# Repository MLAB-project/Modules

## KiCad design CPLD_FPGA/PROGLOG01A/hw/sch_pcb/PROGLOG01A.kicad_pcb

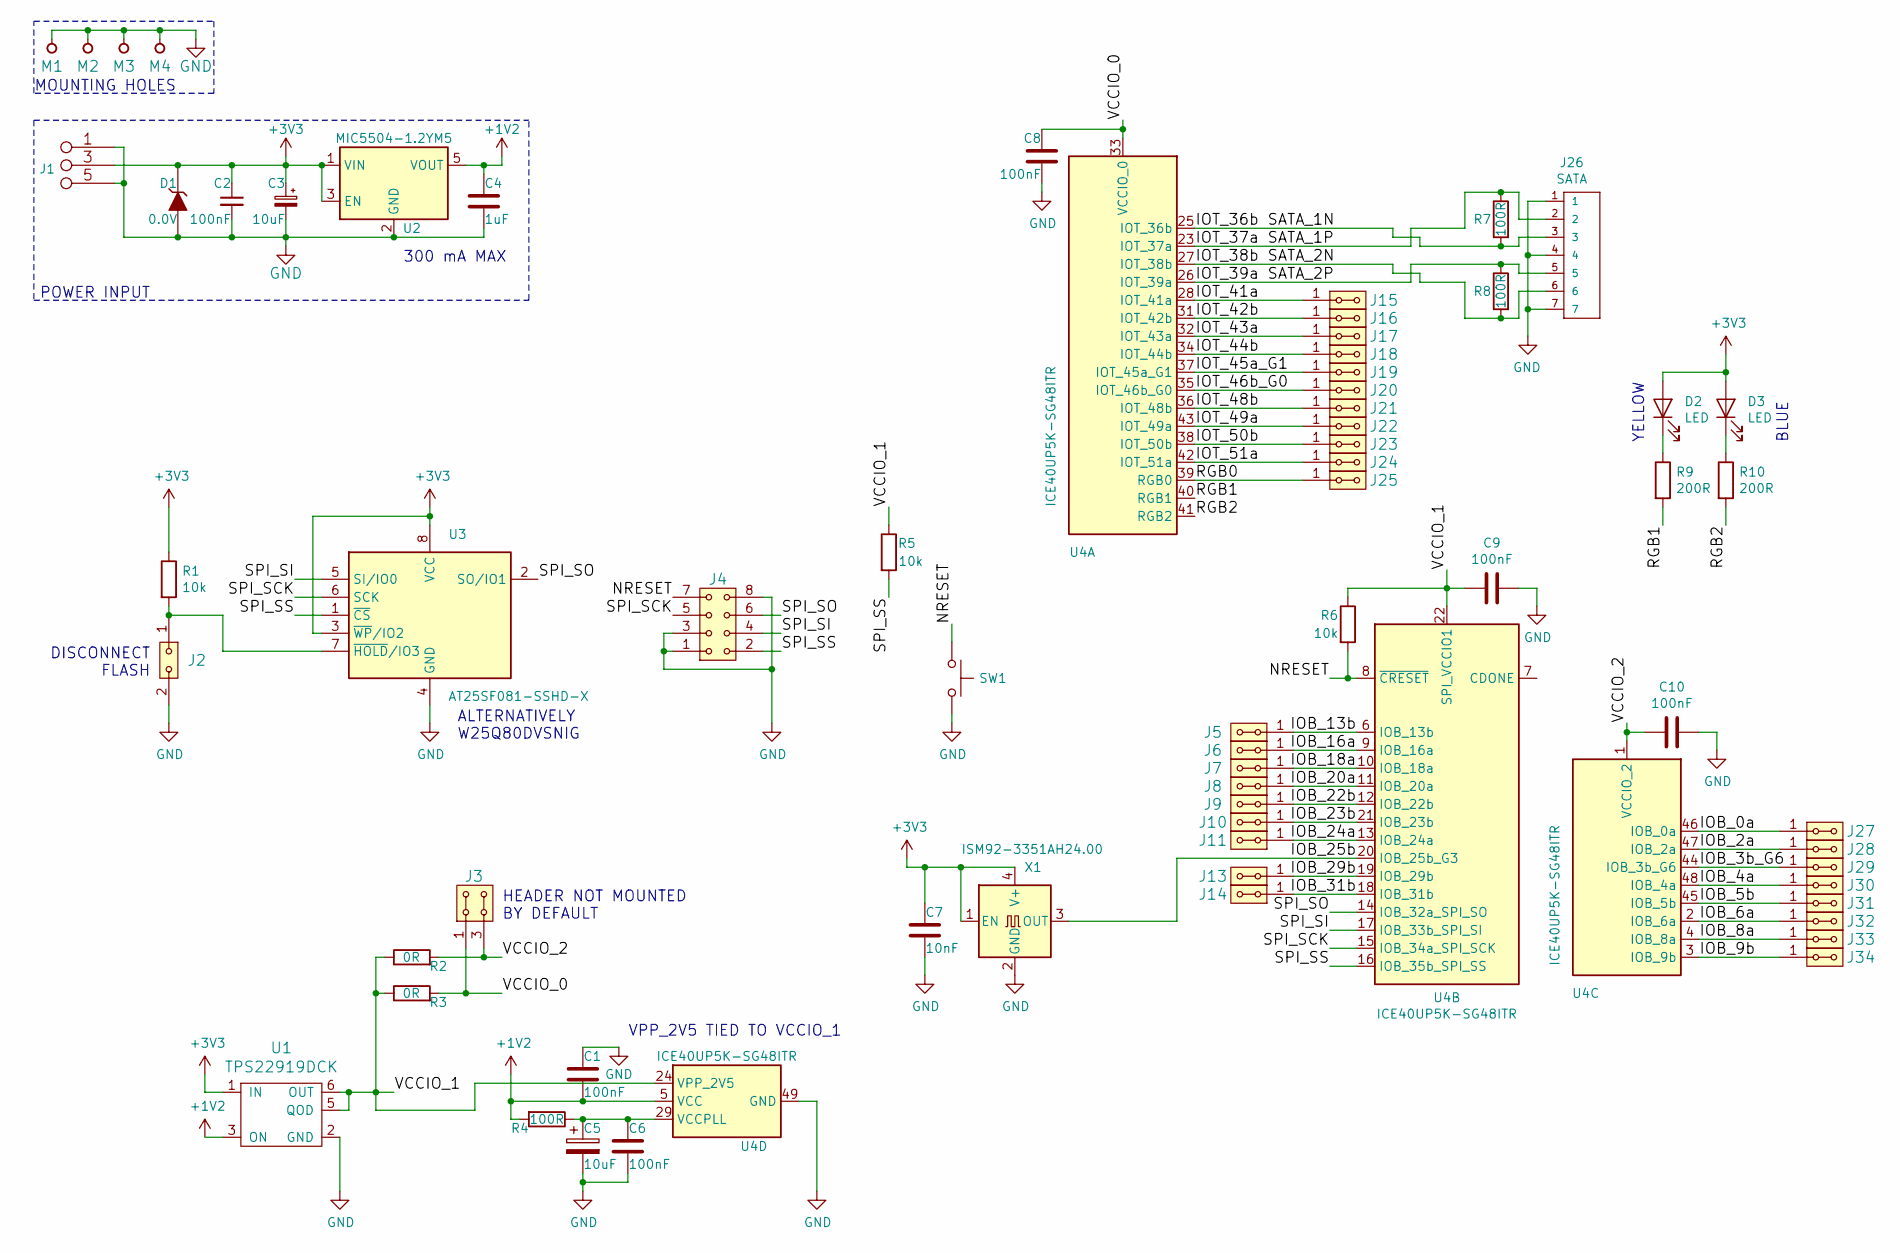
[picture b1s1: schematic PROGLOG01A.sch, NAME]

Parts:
C1, C2, C6, C8, C9, C10: 100nF; SMD-0805
C3, C5: 10uF; SMD-0805
C4: 1uF; SMD-0805
C7: 10nF; SMD-0805
D1: 0.0V; Diode-MiniMELF_Standard
D2, D3: LED; LED_1206
J1: JUMP_3X2; Straight_2x03
J2: HEADER_2x01; Straight_2x01
J3: HEADER_2x02_PARALLEL; Straight_2x02
J4: HEADER_2x04; Straight_2x04
J5, J6, J7, J8, J9, J10, J11, J13, J14, J15, J16, J17, J18, J19, J20, J21, J22, J23, J24, J25, J27, J28, J29, J30, J31, J32, J33, J34: HEADER_2x01_PARALLEL; Straight_2x01
J26: SATA; SATA-7_THT_VERT_2
M1, M2, M3, M4: HOLE; MountingHole_3mm
R1, R5, R6: 10k; SMD-0805
R2, R3: 0R; SMD-0805
R4, R7, R8: 100R; SMD-0805
R9, R10: 200R; SMD-0805
SW1: SW_Push; SW_PUSH_SMALL
U1: TPS22919DCK; SOT-363_SC-70-6_Handsoldering
U2: MIC5504-1.2YM5; SOT-23-5_HandSoldering
U3: AT25SF081-SSHD-X; SOIC-8_3.9x4.9mm_Pitch1.27mm
U4: ICE40UP5K-SG48ITR; QFN-48-1EP_7x7mm_P0.5mm_EP5.6x5.6mm
X1: ISM92-3351AH24.00; ISM92

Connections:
+1V2: C1.2, C4.1, R4.2, U1.3 (ON), U2.5 (VOUT), U4.5 (VCC), U4.30 (VCC)
+3V3: C2.1, C3.1, C7.1, D1.1 (K), D2.2 (A), D3.2 (A), J1.3 (4), J1.4, R1.1, U1.1 (IN), U2.1 (VIN), U2.3 (EN), U3.3 (~WP~/IO2), U3.8 (VCC), X1.1 (EN), X1.4 (V+)
/IOB_0a: J27.1, J27.2, U4.46 (IOB_0a)
/IOB_2a: J28.1, J28.2, U4.47 (IOB_2a)
/IOB_3b_G6: J29.1, J29.2, U4.44 (IOB_3b_G6)
/IOB_4a: J30.1, J30.2, U4.48 (IOB_4a)
/IOB_5b: J31.1, J31.2, U4.45 (IOB_5b)
/IOB_6a: J32.1, J32.2, U4.2 (IOB_6a)
/IOB_8a: J33.1, J33.2, U4.4 (IOB_8a)
/IOB_9b: J34.1, J34.2, U4.3 (IOB_9b)
/IOB_13b: J5.1, J5.2, U4.6 (IOB_13b)
/IOB_16a: J6.1, J6.2, U4.9 (IOB_16a)
/IOB_18a: J7.1, J7.2, U4.10 (IOB_18a)
/IOB_20a: J8.1, J8.2, U4.11 (IOB_20a)
/IOB_22b: J9.1, J9.2, U4.12 (IOB_22b)
/IOB_23b: J10.1, J10.2, U4.21 (IOB_23b)
/IOB_24a: J11.1, J11.2, U4.13 (IOB_24a)
/IOB_25b: U4.20 (IOB_25b_G3), X1.3 (OUT)
/IOB_29b: J13.1, J13.2, U4.19 (IOB_29b)
/IOB_31b: J14.1, J14.2, U4.18 (IOB_31b)
/IOT_41a: J15.1, J15.2, U4.28 (IOT_41a)
/IOT_42b: J16.1, J16.2, U4.31 (IOT_42b)
/IOT_43a: J17.1, J17.2, U4.32 (IOT_43a)
/IOT_44b: J18.1, J18.2, U4.34 (IOT_44b)
/IOT_45a_G1: J19.1, J19.2, U4.37 (IOT_45a_G1)
/IOT_46b_G0: J20.1, J20.2, U4.35 (IOT_46b_G0)
/IOT_48b: J21.1, J21.2, U4.36 (IOT_48b)
/IOT_49a: J22.1, J22.2, U4.43 (IOT_49a)
/IOT_50b: J23.1, J23.2, U4.38 (IOT_50b)
/IOT_51a: J24.1, J24.2, U4.42 (IOT_51a)
/NRESET: J4.7, R6.2, SW1.1, U4.8 (~CRESET)
/RGB0: J25.1, J25.2, U4.39 (RGB0)
/RGB1: R9.2, U4.40 (RGB1)
/RGB2: R10.2, U4.41 (RGB2)
/SATA_1N: J26.3, R7.2, U4.25 (IOT_36b)
/SATA_1P: J26.2, R7.1, U4.23 (IOT_37a)
/SATA_2N: J26.6, R8.2, U4.27 (IOT_38b)
/SATA_2P: J26.5, R8.1, U4.26 (IOT_39a)
/SPI_SCK: J4.5, U3.6 (SCK), U4.15 (IOB_34a_SPI_SCK)
/SPI_SI: J4.4, U3.5 (SI/IO0), U4.17 (IOB_33b_SPI_SI)
/SPI_SO: J4.6, U3.2 (SO/IO1), U4.14 (IOB_32a_SPI_SO)
/SPI_SS: J4.2, R5.2, U3.1 (~CS), U4.16 (IOB_35b_SPI_SS)
/VCCIO_0: C8.1, J3.1, J3.2, R3.2, U4.33 (VCCIO_0)
/VCCIO_1: C9.2, R2.1, R3.1, R5.1, R6.1, U1.5 (QOD), U1.6 (OUT), U4.22 (SPI_VCCIO1), U4.24 (VPP_2V5)
/VCCIO_2: C10.2, J3.3, J3.4, R2.2, U4.1 (VCCIO_2)
GND: C1.1, C2.2, C3.2, C4.2, C5.2, C6.2, C7.2, C8.2, C9.1, C10.1, D1.2 (A), J1.1 (2), J1.2, J1.5 (6), J1.6, J2.2, J4.1, J4.3, J4.8, J26.1, J26.4, J26.7, M1.1, M2.1, M3.1, M4.1, SW1.2, U1.2 (GND), U2.2 (GND), U3.4 (GND), U4.49 (GND), X1.2 (GND)
unnamed: C5.1, C6.1, R4.1, U4.29 (VCCPLL)
unnamed: D2.1 (K), R9.1
unnamed: D3.1 (K), R10.1
unnamed: J2.1, R1.2, U3.7 (~HOLD~/IO3)

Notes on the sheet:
POWER INPUT
MOUNTING HOLES
300 mA MAX
VPP_2V5 TIED TO VCCIO_1
HEADER NOT MOUNTED BY DEFAULT
ALTERNATIVELY W25Q80DVSNIG
DISCONNECT FLASH
YELLOW
BLUE

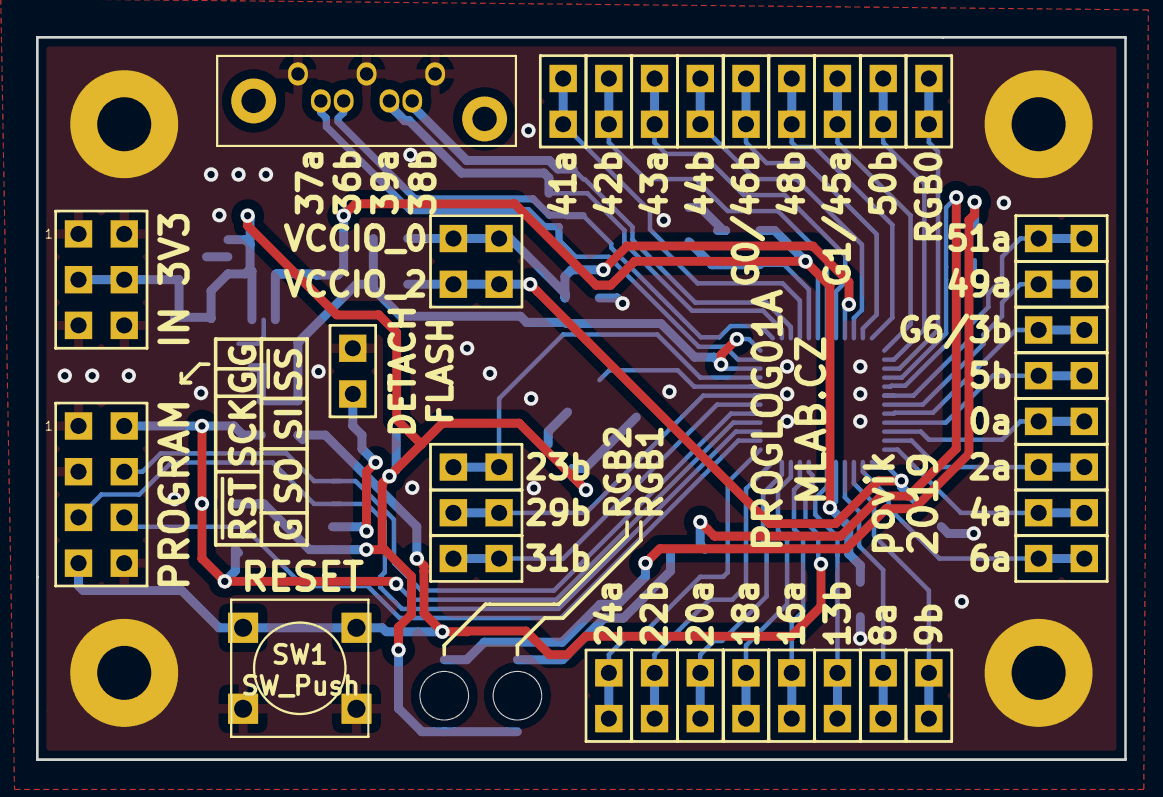
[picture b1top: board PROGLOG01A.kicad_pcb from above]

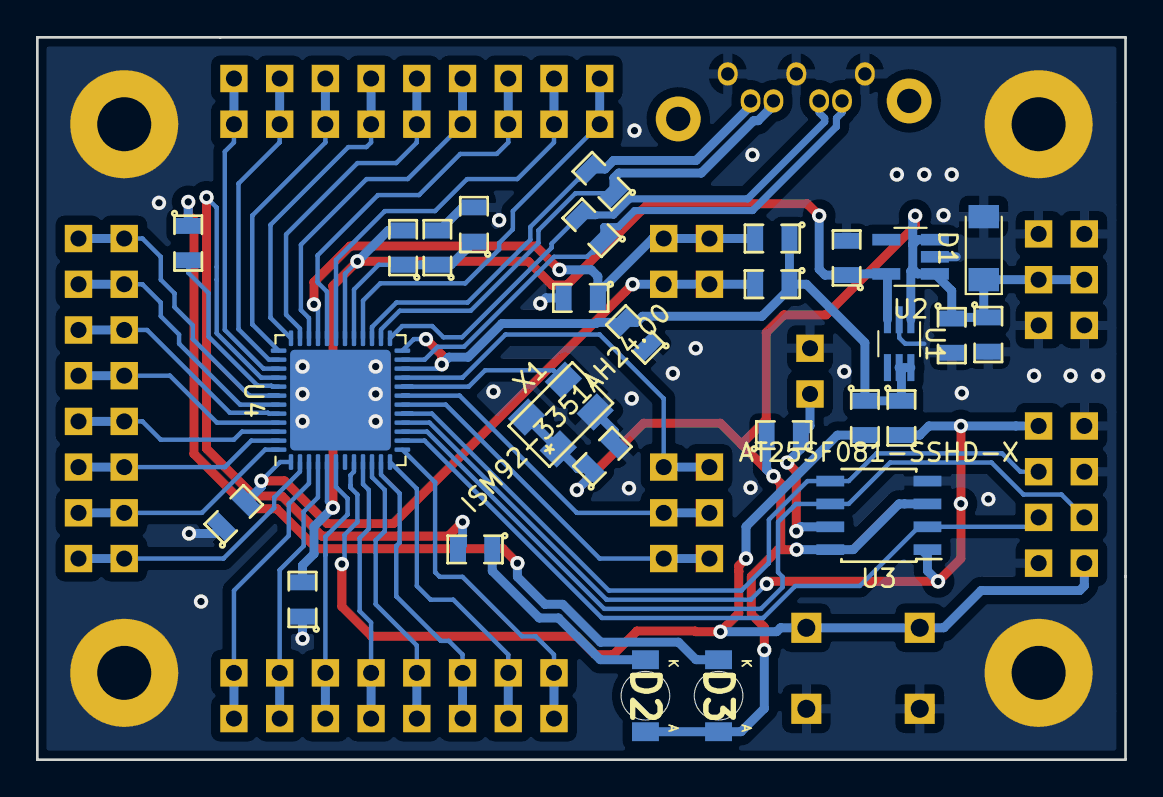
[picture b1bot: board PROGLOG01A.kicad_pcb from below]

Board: 2 copper layers, 60.5 x 40.1 mm, 66 parts (28 on the bottom side), 50 nets.

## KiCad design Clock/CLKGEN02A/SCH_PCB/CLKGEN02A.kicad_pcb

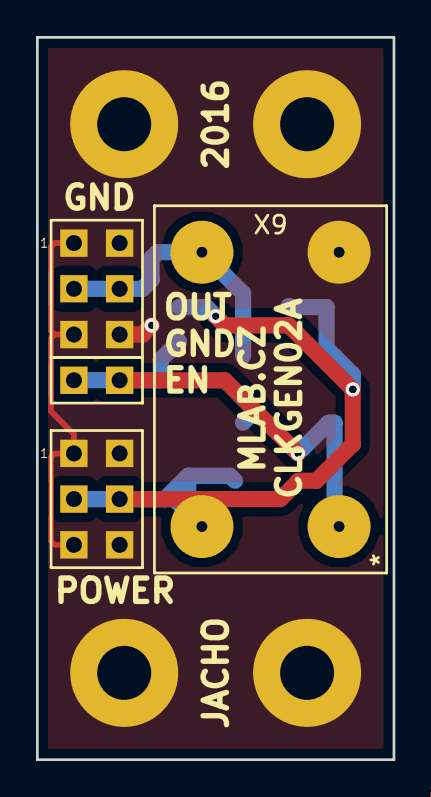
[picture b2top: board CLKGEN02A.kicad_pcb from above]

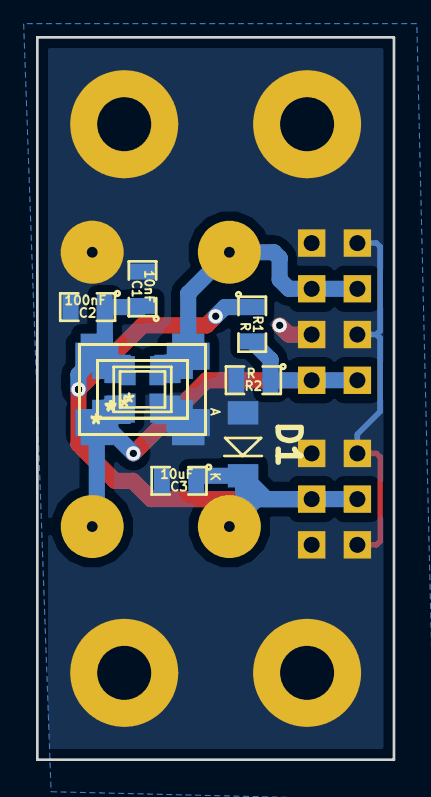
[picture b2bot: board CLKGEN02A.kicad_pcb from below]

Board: 2 copper layers, 19.8 x 40.1 mm, 21 parts (13 on the bottom side), 4 nets.

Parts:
C1: 10nF; SMD-0805
C2: 100nF; SMD-0805
C3: 10uF; SMD-0805
D1: BZV55C; Diode-MiniMELF_Standard
J1, J3: JUMP_3X2; Straight_2x03
J2: JUMP_2x1; Straight_1x02
M1, M2, M3, M4: HOLE; MountingHole_3mm
R1, R2: R; SMD-0805
X1: ASFL1, ASFLK; ASFL1
X2: CFPS-72,CFPS-73; CFPS-72,73
X3: ISM92
X4: ISM97
X6: I533_I534_I733_I734_Series; I533_1534_1733_1734
X7: ISM81
X8: ISM95
X9: OSC-F

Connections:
/EN: J2.1, J2.2, R1.2, R2.1, X1.1, X2.1, X3.1, X4.1, X6.1, X7.1, X8.1, X9.1
/OUT: J3.3, J3.4, X1.3, X2.3, X3.3, X4.3, X6.3, X7.3, X8.3, X9.3
GND: C1.2, C2.2, C3.2, D1.2, J1.1, J1.2, J1.5, J1.6, J3.1, J3.2, J3.5, J3.6, M1.1, M2.1, M3.1, M4.1, R2.2, X1.2, X2.2, X3.2, X4.2, X6.2, X7.2, X8.2, X9.2
VCC: C1.1, C2.1, C3.1, D1.1, J1.3, J1.4, R1.1, X1.4, X2.4, X3.4, X4.4, X6.4, X7.4, X8.4, X9.4

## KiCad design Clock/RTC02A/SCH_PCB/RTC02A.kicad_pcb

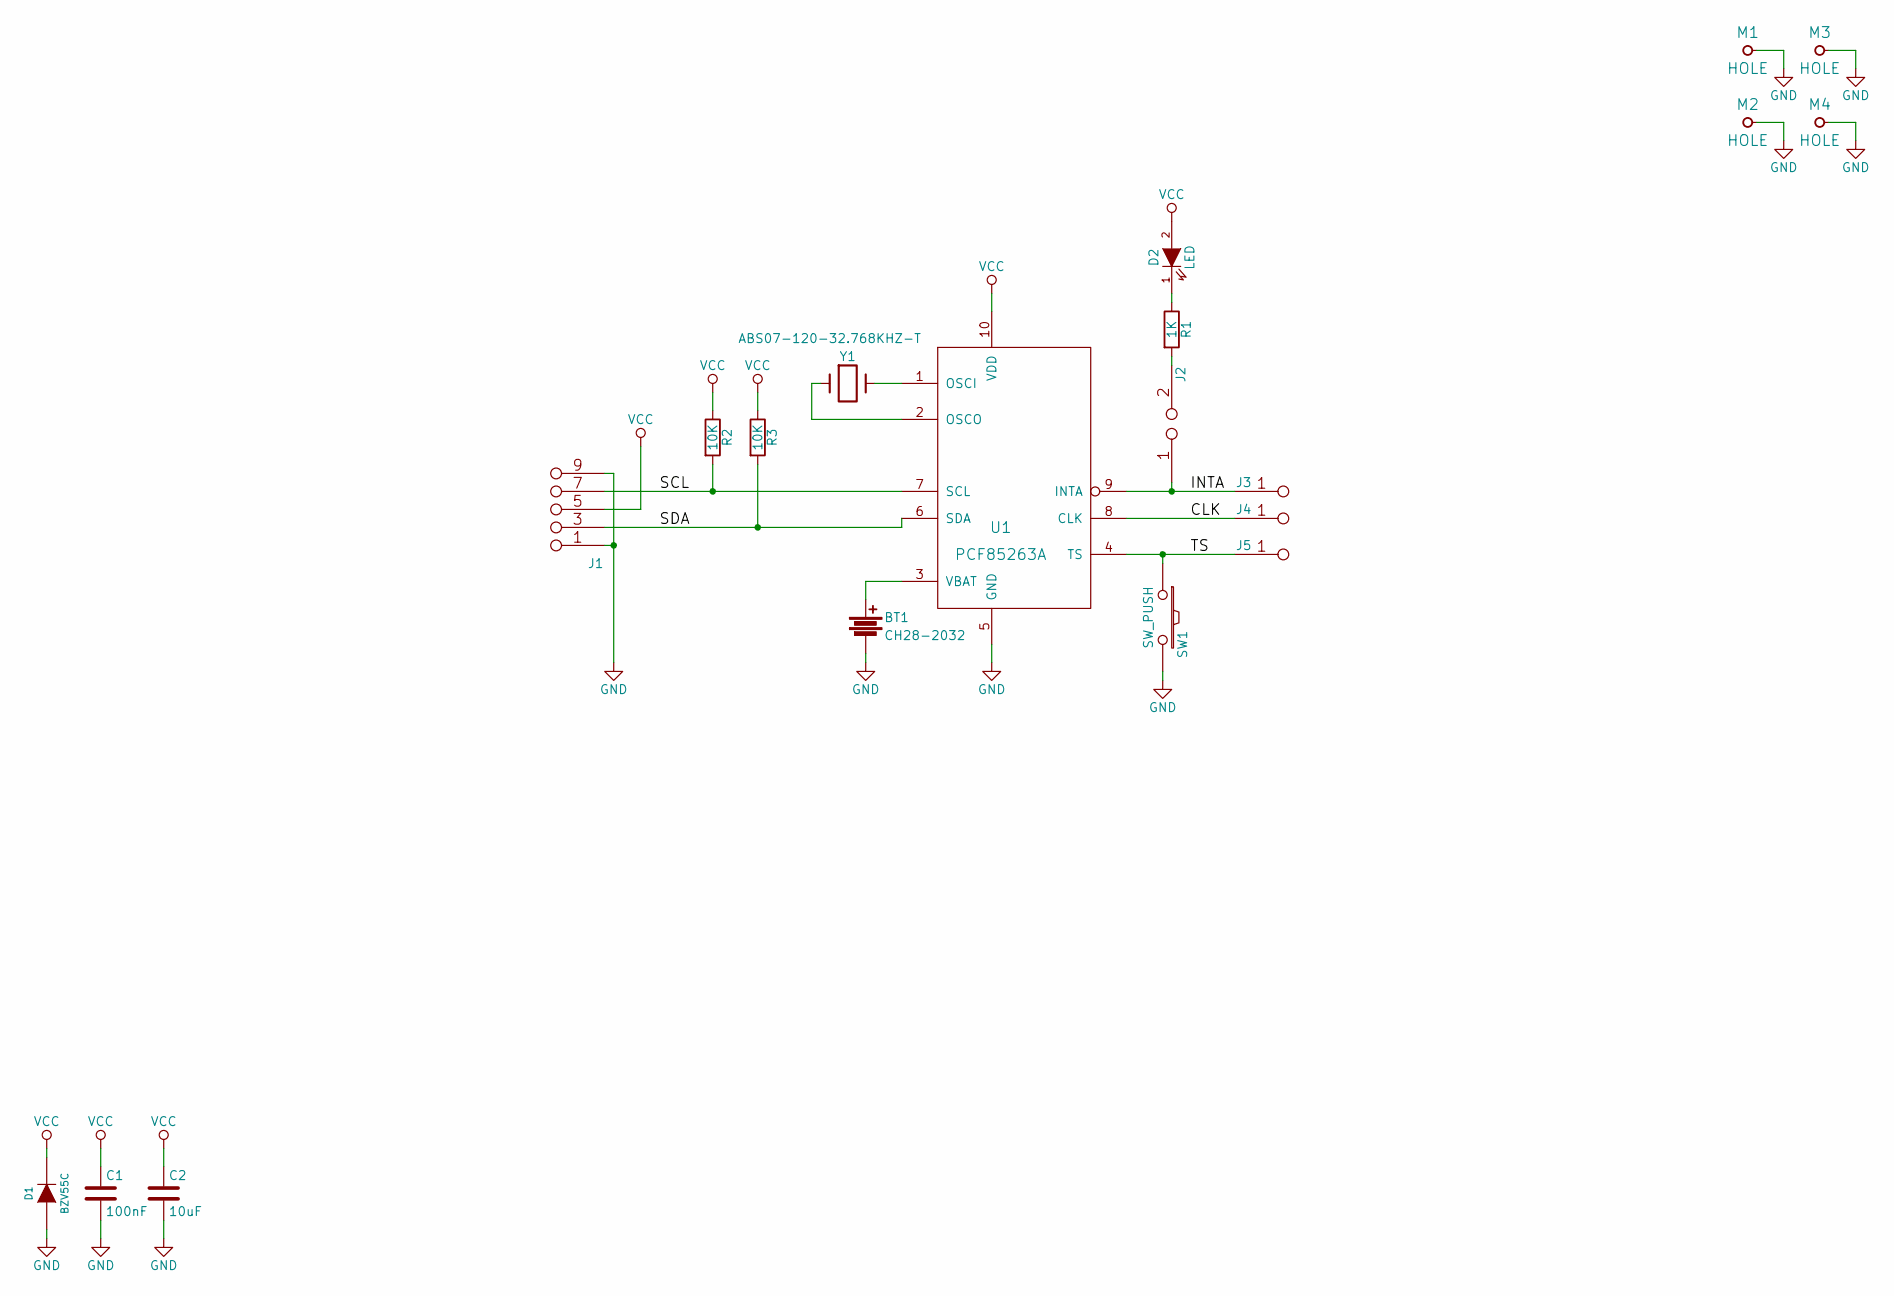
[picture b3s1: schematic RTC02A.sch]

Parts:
BT1: CH28-2032
C1: 100nF; SMD-0805
C2: 10uF; SMD-0805
D1: BZV55C; Diode-MiniMELF_Standard
D2: LED; LED_1206
J1: JUMP_5X2; Straight_2x05
J2: JUMP2_2x1; Straight_2x01
J3, J4, J5: JUMP_2x1; Straight_2x01
M1, M2, M3, M4: HOLE; MountingHole_3mm
R1: 1K; SMD-0805
R2, R3: 10K; SMD-0805
SW1: SW_PUSH; SW_PUSH_SMALL
U1: PCF85263A; TSSOP-10_3x3mm_Pitch0.5mm
Y1: ABS07-120-32.768KHZ-T; ABS07

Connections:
/CLK: J4.1, J4.2, U1.8 (CLK)
/INTA: J2.1, J3.1, J3.2, U1.9 (INTA)
/SCL: J1.7, J1.8 (7), R2.2, U1.7 (SCL)
/SDA: J1.3 (4), J1.4, R3.2, U1.6 (SDA)
/TS: J5.1, J5.2, SW1.1, U1.4 (TS)
GND: BT1.2, C1.2, C2.2, D1.2 (A), J1.1 (2), J1.2, J1.9 (10), J1.10, M1.1, M2.1, M3.1, M4.1, SW1.2, U1.5 (GND); also elsewhere on the board
unnamed: BT1.1, U1.3 (VBAT)
unnamed: D2.1 (K), R1.1
unnamed: J2.2, R1.2
unnamed: U1.1 (OSCI), Y1.2
unnamed: U1.2 (OSCO), Y1.1
VCC: C1.1, C2.1, D1.1 (K), D2.2 (A), J1.5 (6), J1.6, R2.1, R3.1, U1.10 (VDD)

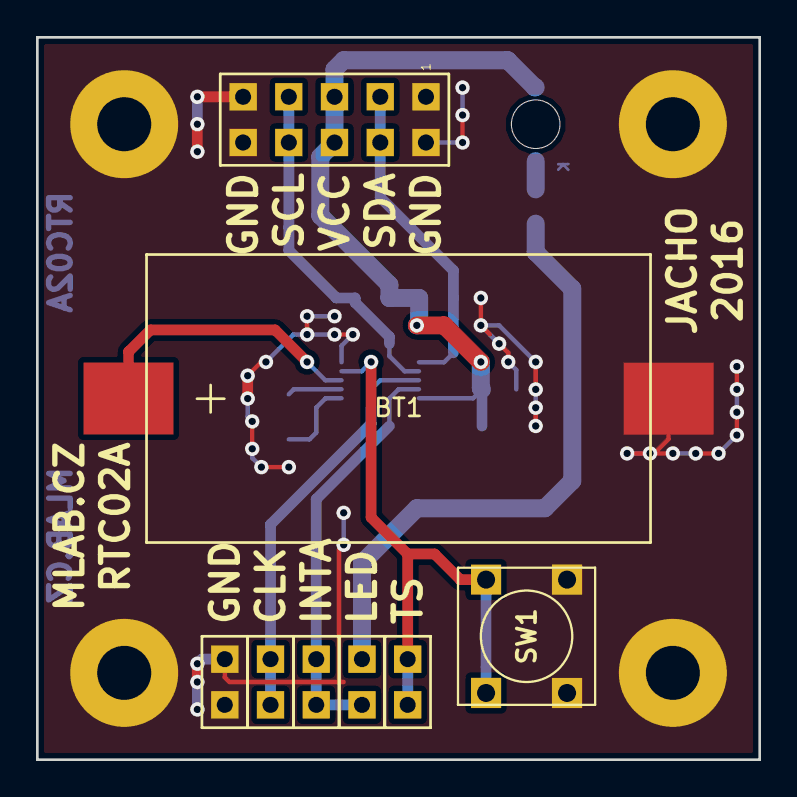
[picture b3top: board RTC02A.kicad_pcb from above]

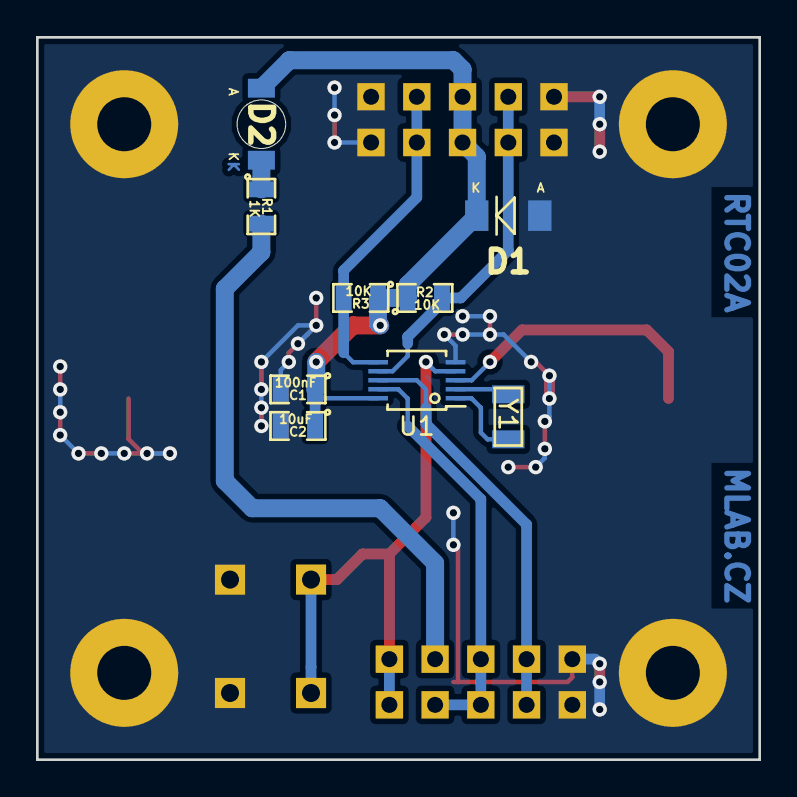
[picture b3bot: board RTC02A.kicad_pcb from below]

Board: 2 copper layers, 40.1 x 40.1 mm, 21 parts (9 on the bottom side), 12 nets.

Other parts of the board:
J6: JUMP_2x1; Straight_2x01

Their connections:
GND: J6.1, J6.2; also elsewhere on the board

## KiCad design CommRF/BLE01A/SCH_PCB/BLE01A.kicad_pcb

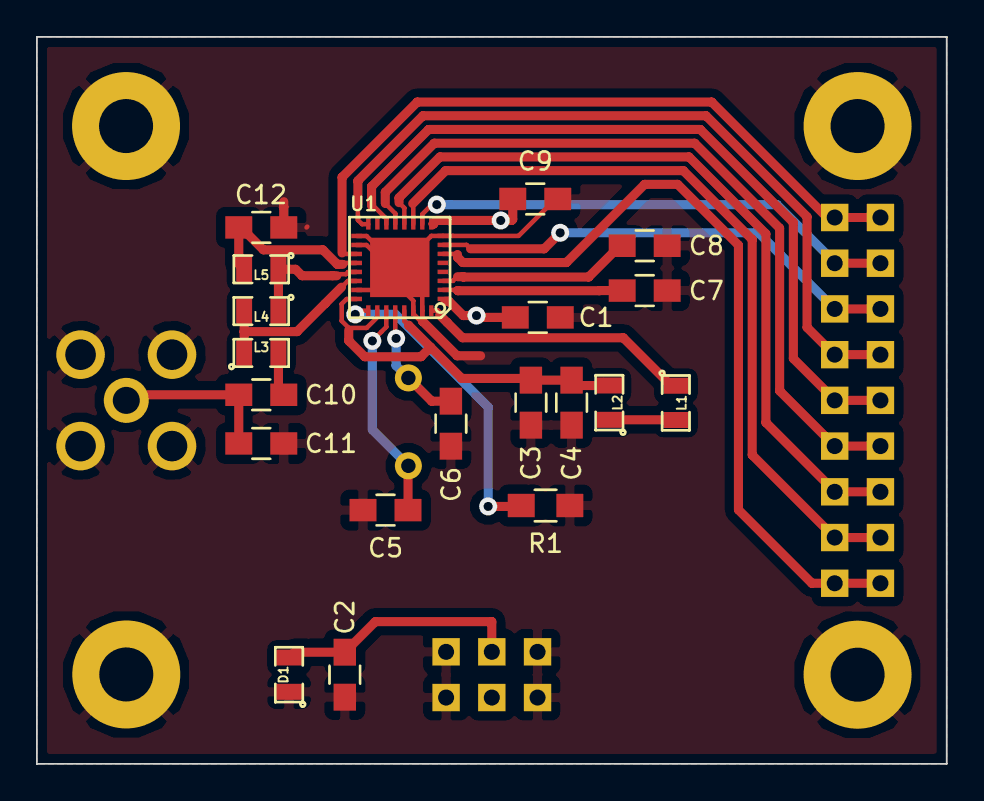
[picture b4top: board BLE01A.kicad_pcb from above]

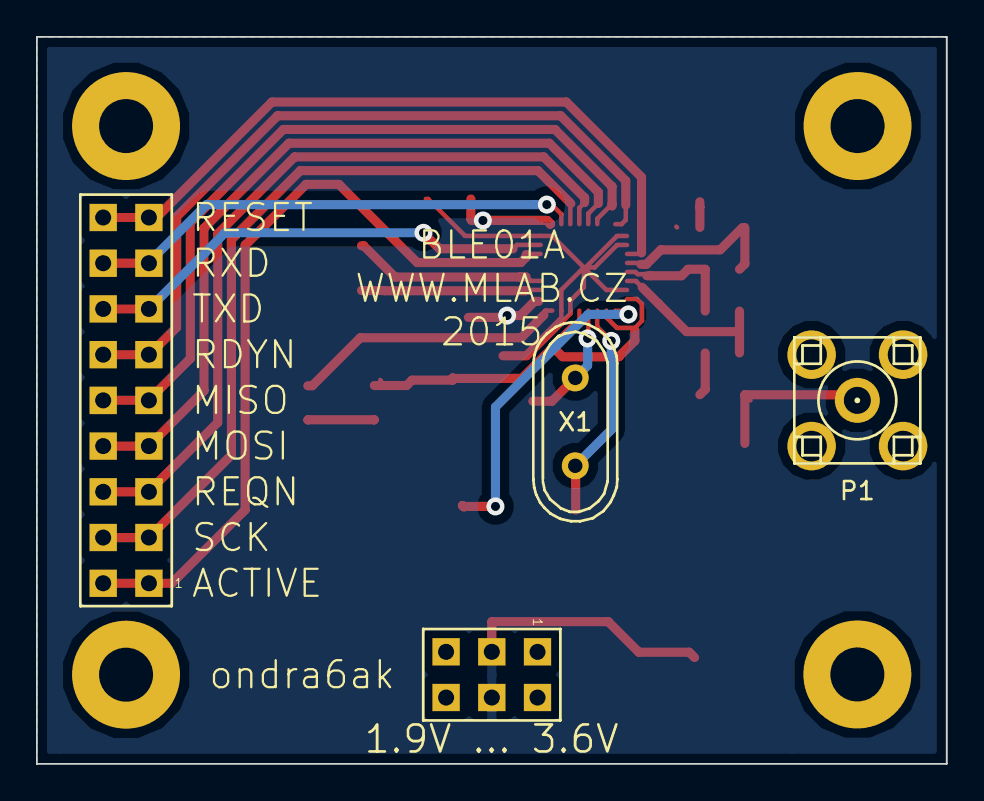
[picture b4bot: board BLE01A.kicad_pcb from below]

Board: 2 copper layers, 50.5 x 40.4 mm, 28 parts (4 on the bottom side), 24 nets.

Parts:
C1, C7, C9: 100nF; C_0805_HandSoldering
C2: 22uF/6.3V; C_0805_HandSoldering
C3: 1nF; C_0805_HandSoldering
C4: 1uF; C_0805_HandSoldering
C5, C6: 12pF; C_0805_HandSoldering
C8: 33nF; C_0805_HandSoldering
C10: 1.8pF; C_0805_HandSoldering
C11: 1.2pF; C_0805_HandSoldering
C12: 2.2nF; C_0805_HandSoldering
D1: 1N4007; SMD-0805
J1: 1.9V ... 3.6V; Straight_2x03
J2: HEADER_2x09_PARALLEL; Straight_2x09
L1: 10uH; SMD-0805
L2: 15nH; SMD-0805
L3: 3.9nH; SMD-0805
L4: 8.2nH; SMD-0805
L5: 5.6nH; SMD-0805
M1, M2, M3, M4: HOLE; SolderWirePad_single_2-5mmDrill
P1: SMA6251A13G50
R1: 22k; R_0805_HandSoldering
U1: NRF8001; QFN-32-1EP
X1: 16MHz; Crystal_HC49-U_Vertical

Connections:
/ACTIVE: J2.1, J2.2, U1.6
/ANT1: L4.1, L5.1, U1.21
/ANT2: L3.1, L4.2, U1.22
/AVDD: C3.1, C4.1, L2.2, U1.24, U1.26, U1.29
/MISO: J2.9, J2.10, U1.14
/MOSI: J2.7, J2.8, U1.13
/RDYN: J2.11, J2.12, U1.16
/REQN: J2.5, J2.6, U1.12
/RESET: J2.17, J2.18, U1.19
/RXD: J2.15, J2.16, U1.10
/SCK: J2.3, J2.4, U1.11
/TXD: J2.13, J2.14, U1.7
/VDD_PA: C12.1, L5.2, U1.20
/XC1: C6.1, U1.28, X1.2
/XC2: C5.1, U1.27, X1.1
GND: C1.2, C2.2, C3.2, C4.2, C5.2, C6.2, C7.2, C8.2, C9.2, C11.2, C12.2, D1.1, J1.1, J1.2, J1.5, J1.6, M1.1, M2.1, M3.1, M4.1, P1.2, R1.1, U1.8, U1.17, U1.18, U1.23, U1.30, U1.31, U1.33
unnamed: C7.1, U1.2
unnamed: C8.1, U1.3
unnamed: C10.1, L3.2
unnamed: C10.2, C11.1, P1.1
unnamed: L1.1, U1.32
unnamed: L1.2, L2.1
unnamed: R1.2, U1.25
VCC: C1.1, C2.1, C9.1, D1.2, J1.3, J1.4, U1.1, U1.9

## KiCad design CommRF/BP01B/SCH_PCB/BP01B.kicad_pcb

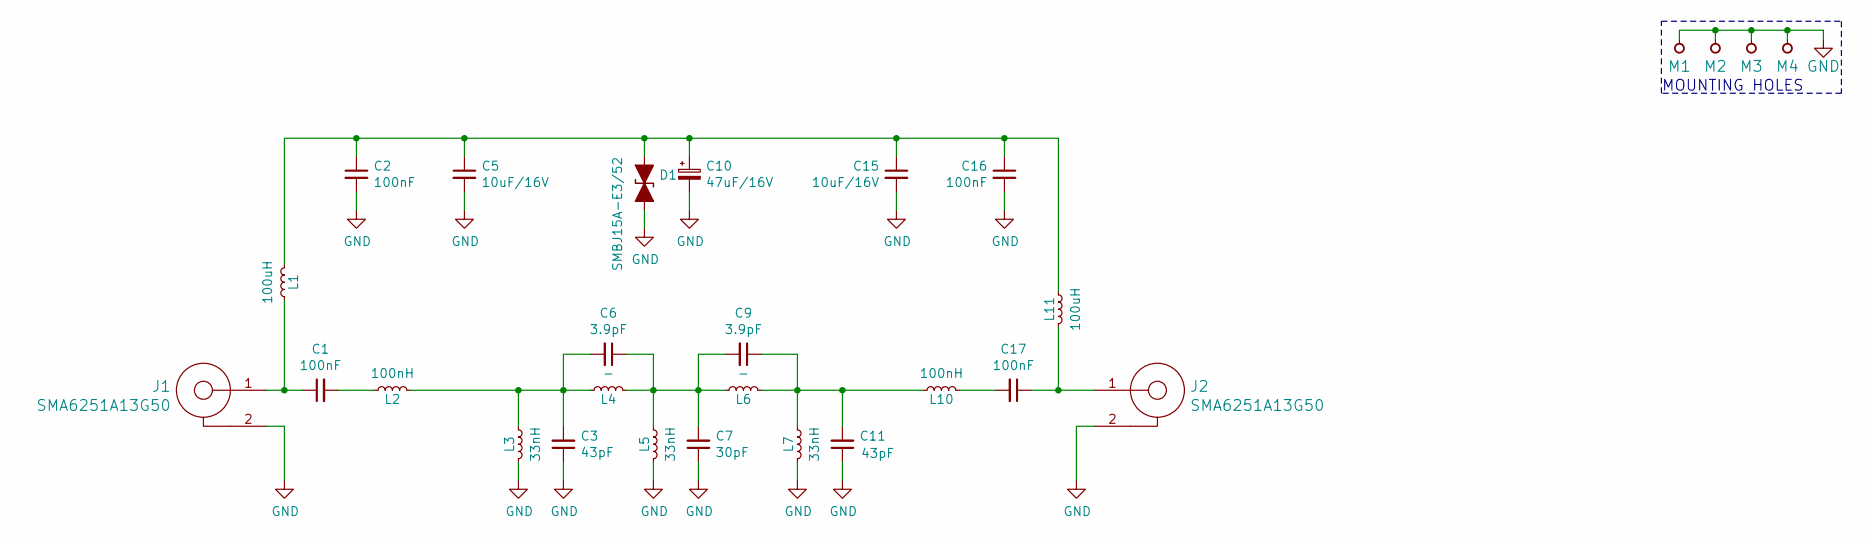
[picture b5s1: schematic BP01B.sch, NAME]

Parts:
C1, C2, C16, C17: 100nF; SMD-0805
C3, C11: 43pF; SMD-0805
C5, C15: 10uF/16V; SMD-0805
C6, C9: 3.9pF; SMD-0805
C7: 30pF; SMD-0805
C10: 47uF/16V; TantalC_SizeC_Reflow
D1: SMBJ15A-E3/52; SMB_Standard
J1, J2: SMA6251A13G50
L1, L11: 100uH; SMD-1812
L2, L10: 100nH; SMD-0805
L3, L5, L7: 33nH; SMD-0805
L4, L6: -; SMD-0805
M1, M2, M3, M4: HOLE; MountingHole_3mm

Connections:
GND: C2.2, C3.1, C5.2, C7.1, C10.2, C11.1, C15.2, C16.2, D1.2 (A2), J1.2, J2.2, L3.1, L5.1, L7.1, M1.1, M2.1, M3.1, M4.1
unnamed: C1.1, J1.1, L1.2
unnamed: C1.2, L2.2
unnamed: C3.2, C6.2, L2.1, L3.2, L4.2
unnamed: C6.1, C7.2, C9.2, L4.1, L5.2, L6.2
unnamed: C2.1, C5.1, C10.1, C15.1, C16.1, D1.1 (A1), L1.1, L11.1
unnamed: C9.1, C11.2, L6.1, L7.2, L10.1
unnamed: C17.1, J2.1, L11.2
unnamed: C17.2, L10.2

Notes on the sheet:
MOUNTING HOLES

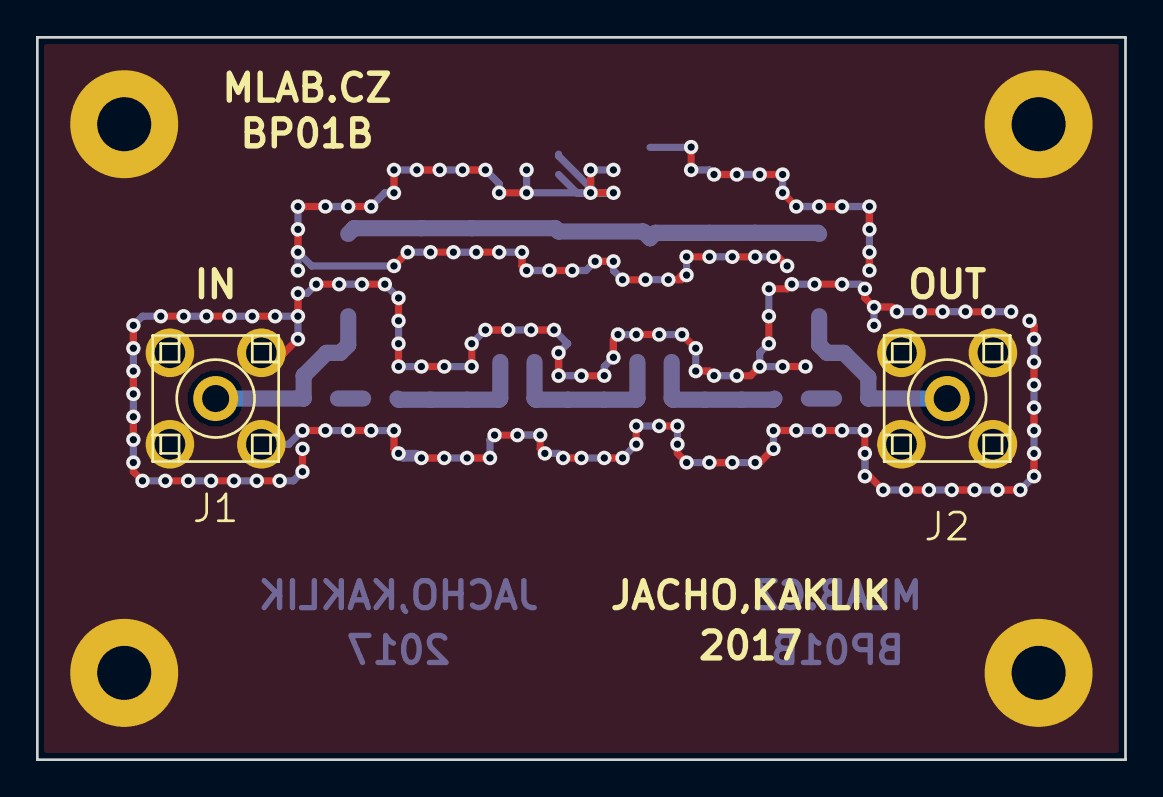
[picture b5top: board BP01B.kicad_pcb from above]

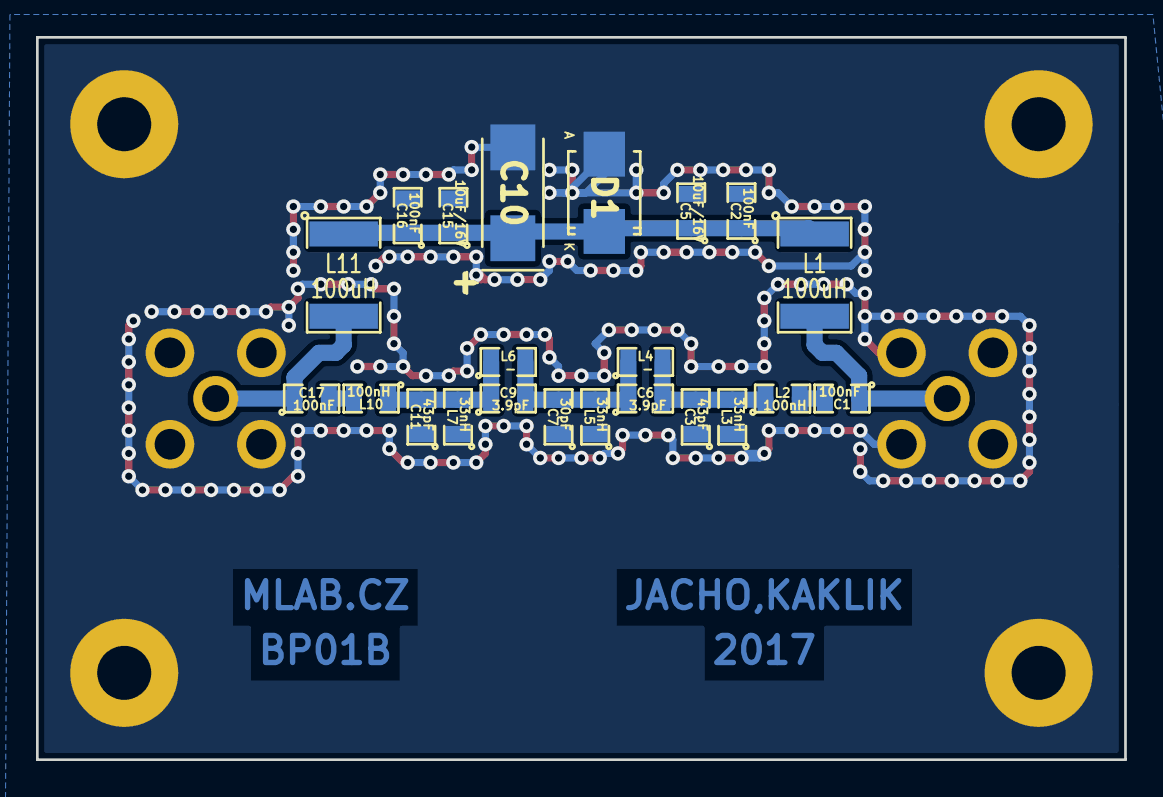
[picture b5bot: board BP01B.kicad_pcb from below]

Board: 2 copper layers, 60.5 x 40.1 mm, 28 parts (22 on the bottom side), 9 nets.

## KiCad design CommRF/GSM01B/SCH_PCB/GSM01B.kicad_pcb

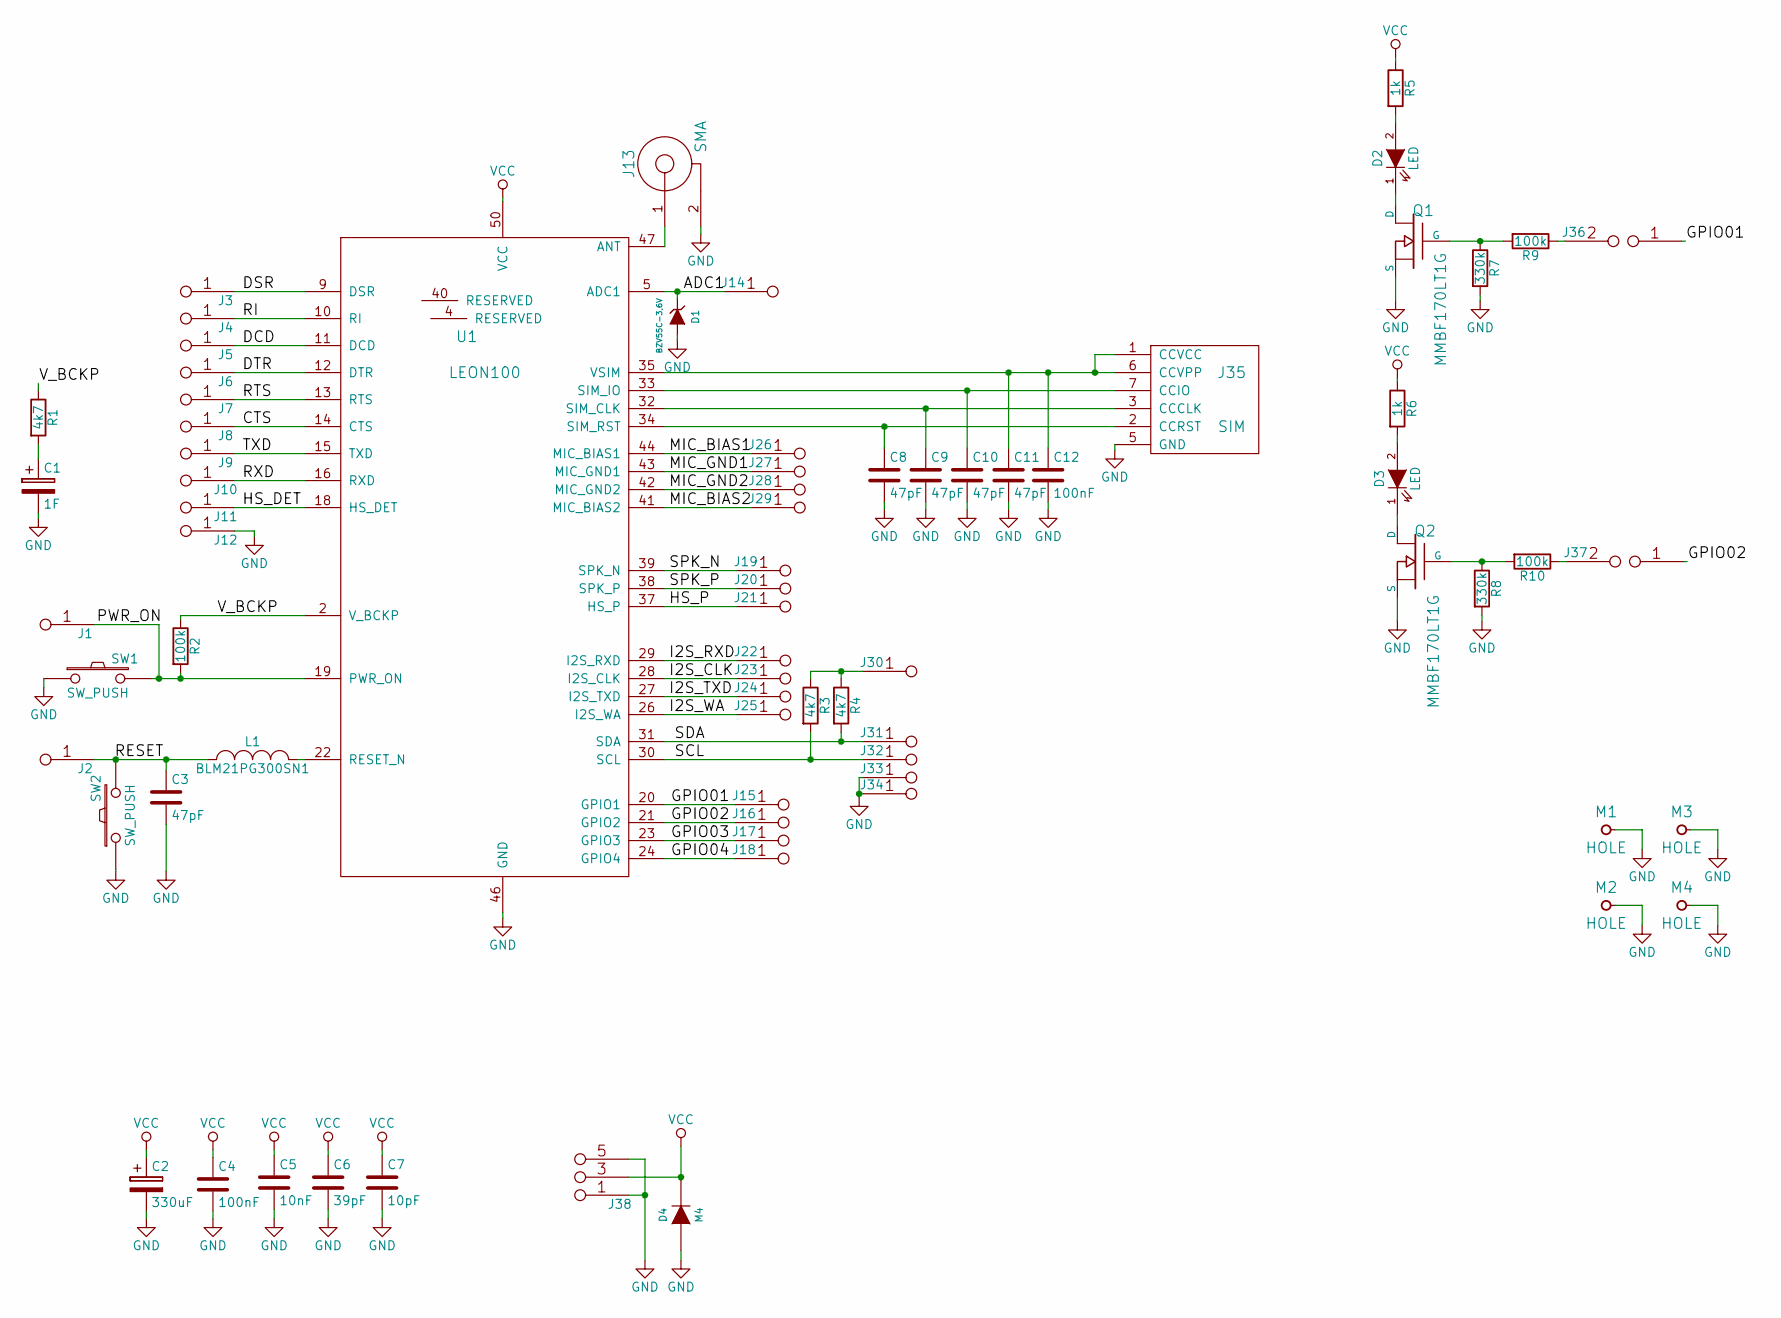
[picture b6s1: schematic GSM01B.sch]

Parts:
C1: 1F; C_Radial_D8_L11.5_P3.5
C2: 330uF; TantalC_SizeD_Reflow
C3, C8, C9, C10, C11: 47pF; SMD-0805
C4, C12: 100nF; SMD-0805
C5: 10nF; SMD-0805
C6: 39pF; SMD-0805
C7: 10pF; SMD-0805
D1: BZV55C-3,6V; Diode-MiniMELF_Standard
D2, D3: LED; LED_1206
D4: M4; Diode-SMA_Standard
J1, J2, J3, J4, J5, J6, J7, J8, J9, J10, J11, J12, J14, J15, J16, J17, J18, J19, J20, J21, J22, J23, J24, J25, J26, J27, J28, J29, J30, J31, J32, J33, J34: JUMP_2x1; Straight_1x02
J13: SMA; SMA6251A13G50
J35: SIM; SIMCN-8P
J36, J37: JUMP2_2x1; Straight_1x02
J38: JUMP_3X2; Straight_2x03
L1: BLM21PG300SN1; SMD-0805
M1, M2, M3, M4: HOLE; MountingHole_3mm
Q1, Q2: MMBF170LT1G; SOT-23
R1, R3, R4: 4k7; SMD-0805
R2, R9, R10: 100k; SMD-0805
R5, R6: 1k; SMD-0805
R7, R8: 330k; SMD-0805
SW1, SW2: SW_PUSH; SW_PUSH_SMALL
U1: LEON100; LEON-G1

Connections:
/ADC1: D1.1 (K), J14.1, J14.2, U1.5 (ADC1)
/CTS: J8.1, J8.2, U1.14 (CTS)
/DCD: J5.1, J5.2, U1.11 (DCD)
/DSR: J3.1, J3.2, U1.9 (DSR)
/DTR: J6.1, J6.2, U1.12 (DTR)
/GPIO01: J15.1, J15.2, J36.1, U1.20 (GPIO1)
/GPIO02: J16.1, J16.2, J37.1, U1.21 (GPIO2)
/GPIO03: J17.1, J17.2, U1.23 (GPIO3)
/GPIO04: J18.1, J18.2, U1.24 (GPIO4)
/HS_DET: J11.1, J11.2, U1.18 (HS_DET)
/HS_P: J21.1, J21.2, U1.37 (HS_P)
/I2S_CLK: J23.1, J23.2, U1.28 (I2S_CLK)
/I2S_RXD: J22.1, J22.2, U1.29 (I2S_RXD)
/I2S_TXD: J24.1, J24.2, U1.27 (I2S_TXD)
/I2S_WA: J25.1, J25.2, U1.26 (I2S_WA)
/MIC_BIAS1: J26.1, J26.2, U1.44 (MIC_BIAS1)
/MIC_BIAS2: J29.1, J29.2, U1.41 (MIC_BIAS2)
/MIC_GND1: J27.1, J27.2, U1.43 (MIC_GND1)
/MIC_GND2: J28.1, J28.2, U1.42 (MIC_GND2)
/PWR_ON: J1.1, J1.2, R2.2, SW1.2, U1.19 (PWR_ON)
/RESET: C3.1, J2.1, J2.2, L1.1, SW2.2
/RI: J4.1, J4.2, U1.10 (RI)
/RTS: J7.1, J7.2, U1.13 (RTS)
/RXD: J10.1, J10.2, U1.16 (RXD)
/SCL: J32.1, J32.2, R3.2, U1.30 (SCL)
/SDA: J31.1, J31.2, R4.2, U1.31 (SDA)
/SPK_N: J19.1, J19.2, U1.39 (SPK_N)
/SPK_P: J20.1, J20.2, U1.38 (SPK_P)
/TXD: J9.1, J9.2, U1.15 (TXD)
/V_BCKP: R1.1, R2.1, U1.2 (V_BCKP)
unnamed: C1.1, R1.2
unnamed: C8.1, J35.2 (CCRST), U1.34 (SIM_RST)
unnamed: C9.1, J35.3 (CCCLK), U1.32 (SIM_CLK)
unnamed: C10.1, J35.7 (CCIO), U1.33 (SIM_IO)
unnamed: C11.1, C12.1, J35.1 (CCVCC), J35.6 (CCVPP), U1.35 (VSIM)
unnamed: D2.1 (K), Q1.D
unnamed: D2.2 (A), R5.2
unnamed: D3.1 (K), Q2.D
unnamed: D3.2 (A), R6.2
unnamed: J13.1, U1.47 (ANT)
unnamed: J30.1, J30.2, R3.1, R4.1
unnamed: J36.2, R9.1
unnamed: J37.2, R10.1
unnamed: L1.2, U1.22 (RESET_N)
unnamed: Q1.G, R7.1, R9.2
unnamed: Q2.G, R8.1, R10.2

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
